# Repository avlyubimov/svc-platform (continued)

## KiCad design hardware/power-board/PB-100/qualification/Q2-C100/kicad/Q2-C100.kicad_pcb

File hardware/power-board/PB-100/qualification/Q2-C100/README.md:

# Q2-C100 Qualification Coupon

Status: `PAUSED DIAGNOSTIC COUPON / FABRICATION BLOCKED`

Q2-C100 is the optional diagnostic laboratory coupon described by
`PB-100-q2-empirical-qualification-plan.md`. It is not PB-100, is not a vehicle
assembly and does not itself authorize `PB-100.kicad_pcb`; ADR-0020 separately
authorizes the full PB-100 Rev.1 EVT layout and its own controlled fab review.
Further coupon development is paused and coupon fabrication is not a prerequisite
for PB-100 EVT layout, fabrication or validation.

The committed KiCad milestone contains:

- the exact `IAUTN15S6N025ATMA1` QDUT and `LM74930QRGERQ1` UCTRL footprints;
- the selected `IAUT300N08S5N012ATMA2` QREV correlation path;
- separate RAW drain, common-source and system-output REDCUBE terminals;
- a direct UCTRL HGATE-to-QDUT gate connection with no Rg or CdV/dt element;
- Kelvin and fixture probe interfaces, isolated heater and TSEP interfaces;
- the routed high-current path, direct HGATE path, DGATE path, controller
  A/OUT Kelvin returns and every remaining pad-to-pad control/fixture
  connection;
- a four-layer, 2.0 mm preliminary stackup boundary and a 2.0 mm RAW_101V
  clearance rule outside the unavoidable reviewed QDUT/RVS/ROV component
  geometries;
- seven independent source spokes per TOLL, 4.0 mm source collection buses,
  reinforced outer-layer power corridors and two five-via transition rows at
  each common-source package boundary;
- exact AEC-Q200 Vishay CRCW-HP RVS/ROV resistors and exact TDK soft-termination
  CCAP, each with an independent controlled alternative.
- exact 2/3/4-position Molex Micro-Fit `436500228`, `436500328` and
  `436500428` board headers and mating harness kits, with the 2.0 mm versus
  recommended 1.57 mm fit mismatch kept open;
- exact Harwin `S1751-46R` SMT probe-attachment hardware, without treating it
  as voltage-, bandwidth- or touch-safety evidence.

KiCad 10.0.4 ERC has zero findings. Board DRC has zero rule violations and
zero unconnected items. CI also pins the four-layer routing set, direct F.Cu HGATE
path, separate internal Kelvin/sense layers, outer-layer power-spine widths,
power-via stitching, 0.20 mm default clearance and 2.0 mm RAW_101V clearance
rule. `Q2-C100-pre-fab-screening.md` reproducibly calculates the known copper
cross-sections, a 3.0453 W straight-corridor hot-loss lower bound and the
194.75 nH absolute waveform-derived loop ceiling. None is a thermal or
extracted-inductance pass. This electrical-routing milestone is not permission
to fabricate.

## Build variants

`CORRELATION-A` populates UCTRL and QREV. UCTRL drives QDUT directly and the
input rise/OV-deglitch behavior is measured.

`FORCED-B` does not populate UCTRL or QREV. The isolated external driver is
connected to JDRIVE pins 1 (gate) and 2 (source Kelvin). Its complete discharge
waveform must be demonstrated to be no stronger than the LM74930-Q1 worst-case
corner before Phase B. The copper between the QDUT gate, JDRIVE and probe points
does not contain a selector, zero-ohm resistor or hidden damping part.

Population differences are controlled by `Q2-C100-assembly-variants.csv`.

## Hard safety boundary

Do not energize or fabricate this revision. Before the status can change to
`FAB-REVIEW`, the supplier stackup/creepage, thermal/current-density and loop-
inductance reviews, 2.0 mm Micro-Fit fit/DFM, exact instrument/probe and
external safety-interface MPNs, interlock behavior, external current limiting,
stored-energy discharge, enclosure/shield, remote trigger, instrument ratings,
heater control and laboratory safety review must close. Board interface
selection is recorded in `Q2-C100-fixture-interface-selection.md` and does not
make exposed connectors or test points touch-safe.
Gerber, drill, pick-and-place and manufacturing ZIP files are prohibited in the
current state.

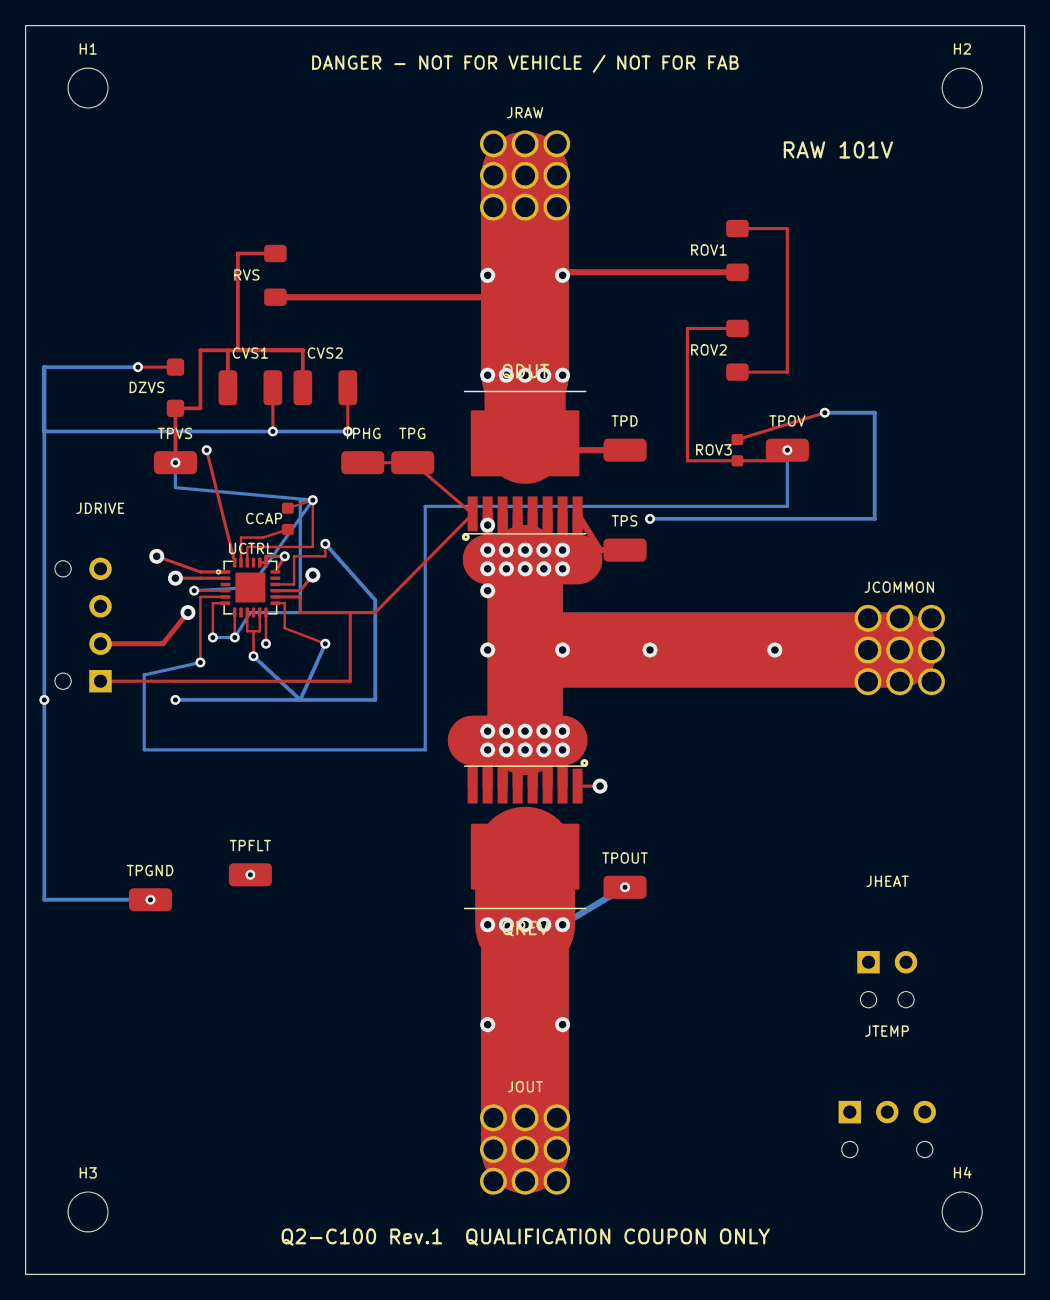
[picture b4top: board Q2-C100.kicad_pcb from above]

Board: 4 copper layers, 80.0 x 100.0 mm, 30 parts (0 on the bottom side), 11 nets.

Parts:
CCAP: CGA3E2X7R1H104K080AE 100nF 50V X7R; R_C_0603_1608Metric
CVS1, CVS2: CGA6N3X7R2A225M230AE 2.2uF 100V X7R; C_1210_3225Metric
DZVS: BZT52H-B56-Q 56V; SOD123F
H1, H2, H3, H4: M3 NPTH; MountingHole_M3_NPTH
JCOMMON: 786202073 REDCUBE M3 130A COMMON; REDCUBE_786202073_3x3_P2.54
JDRIVE: 436500428 MICRO-FIT 4POS DRIVER; MicroFit_43650_0428_Vertical_R90
JHEAT: 436500228 MICRO-FIT 2POS HEATER; MicroFit_43650_0228_Vertical
JOUT: 786202073 REDCUBE M3 130A OUT; REDCUBE_786202073_3x3_P2.54
JRAW: 786202073 REDCUBE M3 130A RAW; REDCUBE_786202073_3x3_P2.54
JTEMP: 436500328 MICRO-FIT 3POS TEMP; MicroFit_43650_0328_Vertical
QDUT: IAUTN15S6N025ATMA1; PG-HSOF-8-1_TOLL_Infineon
QREV: IAUT300N08S5N012ATMA2; PG-HSOF-8-1_TOLL_Infineon
ROV1, ROV2: CRCW120642K2FKEAHP 42.2k 1%; R_1206_3216Metric
ROV3: CRCW06031K00FKEAHP 1.00k 1%; R_C_0603_1608Metric
RVS: CRCW120610K0FKEAHP 10.0k 1%; R_1206_3216Metric
TPD: S1751-46R QDUT_DRAIN_KELVIN; Harwin_S1751-46R
TPFLT: S1751-46R FAULT_PROBE; Harwin_S1751-46R
TPG: S1751-46R QDUT_GATE_KELVIN; Harwin_S1751-46R
TPGND: S1751-46R PROBE_GND; Harwin_S1751-46R
TPHG: S1751-46R UCTRL_HGATE_PROBE; Harwin_S1751-46R
TPOUT: S1751-46R SYSTEM_OUT_PROBE; Harwin_S1751-46R
TPOV: S1751-46R OV_TRIGGER_PROBE; Harwin_S1751-46R
TPS: S1751-46R QDUT_SOURCE_KELVIN; Harwin_S1751-46R
TPVS: S1751-46R CTRL_VS_PROBE; Harwin_S1751-46R
UCTRL: LM74930QRGERQ1; VQFN-24_RGE_4x4mm_P0.5mm_EP2.4mm

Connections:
COMMON_SOURCE: JCOMMON.1 (POWER), JDRIVE.2 (SOURCE_K), QDUT.2 (S), QDUT.3 (S), QDUT.4 (S), QDUT.5 (S), QDUT.6 (S), QDUT.7 (S), QDUT.8 (S), QREV.2 (S), QREV.3 (S), QREV.4 (S), QREV.5 (S), QREV.6 (S), QREV.7 (S), QREV.8 (S), TPS.1 (TP), UCTRL.2 (A), UCTRL.15 (OUT)
CTRL_CAP: CCAP.1, UCTRL.23 (CAP)
CTRL_FLT_N: TPFLT.1 (TP), UCTRL.12 (FLT)
CTRL_OV: ROV2.2, ROV3.1, TPOV.1 (TP), UCTRL.5 (OV)
CTRL_VS: CCAP.2, CVS1.1, CVS2.1, DZVS.1 (K), RVS.2, TPVS.1 (TP), UCTRL.4 (UVLO), UCTRL.6 (EN), UCTRL.7 (MODE), UCTRL.22 (VS)
GND: CVS1.2, CVS2.2, DZVS.2 (A), ROV3.2, TPGND.1 (TP), UCTRL.9 (TMR), UCTRL.11 (ILIM), UCTRL.13 (GND), UCTRL.16 (OVCLAMP)
OV_MID: ROV1.2, ROV2.1
Q2_HGATE: JDRIVE.1 (GATE), QDUT.1 (G), TPG.1 (TP), TPHG.1 (TP), UCTRL.14 (HGATE)
QREV_DGATE: QREV.1 (G), UCTRL.1 (DGATE)
RAW_101V: JRAW.1 (POWER), QDUT.Tab (D), ROV1.1, RVS.1, TPD.1 (TP)
SYSTEM_OUT: JOUT.1 (POWER), QREV.Tab (D), TPOUT.1 (TP), UCTRL.18 (ISCP), UCTRL.19 (CS-), UCTRL.20 (CS+), UCTRL.24 (C)

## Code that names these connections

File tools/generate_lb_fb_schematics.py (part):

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

STM32_NAMES = [
    "PE2", "PE3", "PE4", "PE5", "PE6", "VBAT", "PC13", "PC14-OSC32_IN", "PC15-OSC32_OUT", "VSS",
    "VDD", "PH0-OSC_IN", "PH1-OSC_OUT", "NRST", "PC0", "PC1", "PC2", "PC3", "VSSA", "VREF-",
    "VREF+", "VDDA", "PA0", "PA1", "PA2", "PA3", "VSS", "VDD", "PA4", "PA5", "PA6", "PA7",
    "PC4", "PC5", "PB0", "PB1", "PB2", "PE7", "PE8", "PE9", "PE10", "PE11", "PE12", "PE13",
    "PE14", "PE15", "PB10", "VCAP1", "VSS", "VDD", "PB12", "PB13", "PB14", "PB15", "PD8", "PD9",
    "PD10", "PD11", "PD12", "PD13", "PD14", "PD15", "PC6", "PC7", "PC8", "PC9", "PA8", "PA9",
    "PA10", "PA11-USB_DM", "PA12-USB_DP", "PA13-SWDIO", "VDDUSB", "VSS", "VDD", "PA14-SWCLK",
    "PA15", "PC10", "PC11", "PC12", "PD0", "PD1", "PD2", "PD3", "PD4", "PD5", "PD6", "PD7",
    "PB3-SWO", "PB4", "PB5", "PB6", "PB7", "BOOT0", "PB8", "PB9", "PE0", "VCAP2", "VSS", "VDD",
]


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        "sustained and 381.2 mA service-peak budgets including FB-100 worst-case indication; ADR-0015 "
        "CAN1 FDCAN/read-only ownership with no LB "
        "transceiver; CAN1_TX_ROUTE remains the PB DNP/open route. TCA9539-Q1 maps the ten role-free channel LEDs "
        "and slow UI signals and powers up with all ports as inputs. STM32 PD7 directly drives the timing-critical "
        "LTC3212 LEDEN path. CAN2/LIN/RS485 footprints are DNP by default. USB VBUS uses a 5 V-tolerant "
        "SN74LVC1G17-Q1 digital detector with a defined raw-input pulldown and cannot back-power PB_5V_OUT, "
        "LB_3V3_MAIN, or LB_3V3_IO. Three RADIO_SENSOR_3V3-powered SN74LVC1G125-Q1 buffers isolate both "
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        "keep every E73 digital pin within its unpowered limit. Dedicated top-side test pads expose the module's "
        "own SWDIO, SWDCLK, reset, switched 3.3 V reference, and GND for first programming and recovery. "
        "ADC_REF is sourced and locally decoupled; AGND returns to GND at one documented zero-ohm point. Reviewed footprint "
        "FOG_A_SW_IN and FOG_B_SW_IN are independent protected requests on PA8 and PA9. PB-100 owns the "
        "primary cable-entry suppressor; each LB path has a dry-contact series path, a pull-up, RC filtering, a 4.3 V clamp and an "
        "automotive Schmitt buffer; mutually exclusive DNP transistor paths support a measured 12 V switch variant. "
        "Neither input directly drives an output. Reviewed footprint binding and mechanical envelope remain governed by LB-100-pcb-layout-start-checklist.csv, "
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
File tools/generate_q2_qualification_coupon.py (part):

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                "Correlation build: populate UCTRL and QREV; HGATE is direct to QDUT gate.",
                "Forced build: do not populate UCTRL/QREV; drive QDUT at JDRIVE pins 1/2.",
                "No populated Rg or CdV/dt exists in either accepted build.",
                "RAW_101V may reach 101 V; LM74930 protected pins remain on <=65 V nets.",
                "All pad-to-pad electrical connections are routed; FAB-REVIEW remains open.",
            )
        ),
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    )

    terminal_fp = "Q2C100:REDCUBE_786202073_3x3_P2.54"
    terminal_pin = [("1", "POWER", "RAW_101V")]
    schematic.add(c("JRAW", "786202073 REDCUBE M3 130A RAW", terminal_fp, WURTH_TERMINAL_DS, terminal_pin))
    schematic.add(c("JCOMMON", "786202073 REDCUBE M3 130A COMMON", terminal_fp, WURTH_TERMINAL_DS, [("1", "POWER", "COMMON_SOURCE")]))
    schematic.add(c("JOUT", "786202073 REDCUBE M3 130A OUT", terminal_fp, WURTH_TERMINAL_DS, [("1", "POWER", "SYSTEM_OUT")]))
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    )

    controller_pins = (
        Pin("1", "DGATE", "QREV_DGATE", "output"),
        Pin("2", "A", "COMMON_SOURCE", "input"),
        Pin("3", "SW", None, "no_connect"),
        Pin("4", "UVLO", "CTRL_VS", "input"),
        Pin("5", "OV", "CTRL_OV", "input"),
        Pin("6", "EN", "CTRL_VS", "input"),
        Pin("7", "MODE", "CTRL_VS", "input"),
        Pin("8", "N.C.", None, "no_connect"),
        Pin("9", "TMR", "GND", "input"),
        Pin("10", "IMON", None, "no_connect"),
        Pin("11", "ILIM", "GND", "input"),
        Pin("12", "FLT", "CTRL_FLT_N", "open_collector"),
        Pin("13", "GND", "GND", "power_in"),
        Pin("14", "HGATE", "Q2_HGATE", "output"),
        Pin("15", "OUT", "COMMON_SOURCE", "input"),
        Pin("16", "OVCLAMP", "GND", "input"),
        Pin("17", "N.C.", None, "no_connect"),
        Pin("18", "ISCP", "SYSTEM_OUT", "input"),
        Pin("19", "CS-", "SYSTEM_OUT", "input"),
        Pin("20", "CS+", "SYSTEM_OUT", "input"),
        Pin("21", "N.C.", None, "no_connect"),
        Pin("22", "VS", "CTRL_VS", "power_in"),
        Pin("23", "CAP", "CTRL_CAP", "output"),
        Pin("24", "C", "SYSTEM_OUT", "input"),
        Pin("25", "RTN", None, "no_connect"),
    )
    schematic.add(
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        routes.extend(
            [
                segment(net_codes, "RAW_101V", layer, 7.0, (40.0, 12.0), (40.0, 28.0), "raw-main"),
                segment(net_codes, "COMMON_SOURCE", layer, 6.0, (40.0, 43.0), (40.0, 57.0), "common-spine"),
                segment(net_codes, "COMMON_SOURCE", layer, 6.0, (40.0, 50.0), (70.0, 50.0), "common-terminal"),
                segment(net_codes, "SYSTEM_OUT", layer, 7.0, (40.0, 72.0), (40.0, 90.0), "out-main"),
            ]
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    routes.extend(route_path(net_codes, "CTRL_VS", "F.Cu", 0.3, ((12.0, 35.0), (12.0, 30.65)), "vs-probe"))
    routes.append(signal_via(net_codes, "CTRL_VS", 23.0, 38.0, "vs-controller"))
    routes.extend(route_path(net_codes, "CTRL_VS", "B.Cu", 0.25, ((12.0, 35.0), (12.0, 37.0), (23.0, 38.0)), "vs-controller"))
    routes.extend(route_path(net_codes, "CTRL_VS", "F.Cu", 0.20, ((17.75, 43.0), (17.75, 41.75), (20.0, 41.75), (23.0, 41.75), (23.0, 38.0), (21.0, 38.65)), "vs-pin22-ccap"))
    routes.append(signal_via(net_codes, "CTRL_VS", 13.5, 45.25, "vs-pin4"))
    routes.extend(route_path(net_codes, "CTRL_VS", "F.Cu", 0.20, ((16.0, 45.25), (13.5, 45.25)), "vs-pin4"))
    routes.extend(route_path(net_codes, "CTRL_VS", "B.Cu", 0.25, ((13.5, 45.25), (18.0, 45.0), (23.0, 38.0)), "vs-pin4"))
    routes.append(signal_via(net_codes, "CTRL_VS", 15.0, 49.0, "vs-pin6"))
    routes.append(signal_via(net_codes, "CTRL_VS", 16.75, 49.0, "vs-pin7"))
    routes.extend(route_path(net_codes, "CTRL_VS", "F.Cu", 0.20, ((16.0, 46.25), (15.0, 46.25), (15.0, 49.0)), "vs-pin6"))
    routes.extend(route_path(net_codes, "CTRL_VS", "F.Cu", 0.20, ((16.75, 47.0), (16.75, 49.0)), "vs-pin7"))
    routes.extend(route_path(net_codes, "CTRL_VS", "B.Cu", 0.25, ((15.0, 49.0), (16.75, 49.0), (18.0, 47.0), (22.0, 47.0), (22.0, 38.0), (23.0, 38.0)), "vs-pin6-7"))

    routes.extend(route_path(net_codes, "CTRL_CAP", "F.Cu", 0.20, ((17.25, 43.0), (17.25, 41.0), (19.0, 41.0), (21.0, 40.35)), "cap-local"))

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    routes.extend(route_path(net_codes, "GND", "B.Cu", 0.3, ((18.25, 50.5), (22.0, 54.0)), "gnd-controller-b"))
    routes.extend(route_path(net_codes, "GND", "B.Cu", 0.3, ((24.0, 49.5), (22.0, 54.0)), "gnd-controller-c"))

    # All four protected-side controller sense pins join SYSTEM_OUT on In1.Cu,
    # clear of the existing DGATE route.  TPOUT then joins the B.Cu power path.
    for token, start, fanout in (
        ("out-group", (20.0, 43.75), (20.75, 42.5)),
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    ):
        routes.append(signal_via(net_codes, "SYSTEM_OUT", fanout[0], fanout[1], token))
        routes.extend(route_path(net_codes, "SYSTEM_OUT", "F.Cu", 0.25, (start, fanout), token))
    routes.extend(route_path(net_codes, "SYSTEM_OUT", "F.Cu", 0.25, ((18.75, 43.0), (19.25, 43.0), (19.25, 42.5), (20.75, 42.5)), "out-pins18-20"))
    routes.extend(route_path(net_codes, "SYSTEM_OUT", "In1.Cu", 0.25, ((14.5, 34.0), (20.75, 42.5), (26.0, 43.75), (30.0, 44.0), (30.0, 59.5), (48.0, 59.5), (48.0, 69.0)), "out-sense"))
    routes.extend(route_path(net_codes, "SYSTEM_OUT", "B.Cu", 0.5, ((48.0, 69.0), (43.0, 72.0)), "out-probe"))

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
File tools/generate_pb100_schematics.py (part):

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            "GND",
        )
    )
    schematic.add(resistor("RSN1", "100R DNP Q1 DAMPING", "VBAT_REV_PROT", "Q1_SNUB", dnp=True))
    schematic.add(capacitor("CSN1", "1nF 100V C0G DNP", "Q1_SNUB", "INPUT_COMMON_SOURCE", dnp=True))
    schematic.add(resistor("RSN2", "100R DNP Q2 DAMPING", "VBAT_RAW", "Q2_SNUB", dnp=True))
    schematic.add(capacitor("CSN2", "1nF 200V C0G DNP", "Q2_SNUB", "INPUT_COMMON_SOURCE", dnp=True))

    schematic.add(
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
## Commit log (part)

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2026-06-30 Initial SVC platform structure
2026-06-30 docs: freeze architecture baseline
2026-06-30 docs: select initial component families
2026-06-30 docs: define pb100 current budget
2026-06-30 docs: start implementation after architecture freeze
2026-06-30 hardware: add pb100 schematic input tables
2026-06-30 hardware: select pb100 power path candidates
2026-06-30 hardware: add pb100 preliminary validation
2026-06-30 hardware: add pb100 schematic freeze checklist
2026-06-30 hardware: use external controllers for low-current outputs
2026-06-30 hardware: add pb100 b2b pin map
2026-06-30 hardware: define can1 tx disable input
2026-06-30 hardware: define pb100 input reverse fet strategy
2026-06-30 hardware: define pb100 out2 soa envelope
2026-06-30 test: add pb100 bench validation matrix
2026-06-30 hardware: define pb100 logic power rails
2026-06-30 hardware: define pb100 current telemetry
2026-06-30 hardware: define pb100 thermal telemetry
2026-06-30 hardware: mark pb100 schematic planning ready for review
2026-06-30 hardware: add pb100 kicad preparation plan
2026-06-30 hardware: add pb100 schematic capture contract
2026-06-30 hardware: add pb100 kicad schematic scaffold
2026-06-30 hardware: add pb100 kicad child sheet placeholders
2026-06-30 hardware: add pb100 preliminary kicad symbols
2026-06-30 tools: add pb100 artifact validator
2026-06-30 hardware: define pb100 garage connector plan
2026-06-30 firmware: add power budget service
2026-06-30 firmware: add output manager core
2026-06-30 firmware: add battery protection service
2026-06-30 firmware: add event bus core
2026-06-30 firmware: add can safety guard
2026-06-30 ci: run pb100 and firmware checks
2026-06-30 docs: update project status and validation
2026-06-30 build: add root project checks
2026-06-30 firmware: add system safety coordinator
2026-06-30 firmware: add event dispatcher
2026-06-30 build: rebuild firmware tests on header changes
2026-06-30 firmware: add configuration validator
2026-06-30 tools: validate firmware config json
2026-06-30 firmware: add config json schema
2026-06-30 firmware: add role-based rule actions
2026-06-30 firmware: add rule condition state
2026-06-30 firmware: add in-memory rule runner
2026-06-30 firmware: add initial rule text parser
2026-06-30 firmware: add output pwm state
2026-06-30 firmware: compile rule text to runner
2026-06-30 tools: block pb100 layout artifacts
2026-06-30 docs: refresh project implementation status
2026-06-30 firmware: add telemetry snapshot service
2026-06-30 firmware: use telemetry snapshots in safety paths
2026-06-30 firmware: add event log ring buffer
2026-06-30 tools: run optional pb100 kicad erc
2026-06-30 firmware: add thermal protection service
2026-06-30 firmware: apply thermal cutoff through system safety
2026-06-30 docs: add final readiness gates
2026-06-30 tools: validate pb100 kicad netlist export
2026-06-30 tools: block pb100 kicad role tokens
2026-06-30 hardware: add pb100 symbol mpn readiness gate
2026-06-30 hardware: add pb100 symbol capture worklist
2026-06-30 hardware: add initial pb100 concrete symbols
2026-06-30 hardware: validate pb100 symbol pin evidence
2026-06-30 hardware: add pb100 passive class symbols
2026-06-30 hardware: add pb100 mosfet preliminary symbols
2026-06-30 hardware: add pb100 jpb1 preliminary symbol
2026-06-30 tools: guard pending pb100 symbols
2026-06-30 hardware: add pb100 output fuse symbol
2026-06-30 hardware: map pb100 instances to symbols
2026-06-30 hardware: map pb100 instances to sheets
2026-06-30 hardware: add pb100 kicad sheet manifest
2026-06-30 hardware: add pb100 schematic net domain plan
2026-06-30 production: map pb100 symbols to bom
2026-06-30 hardware: add pb100 schematic readiness contracts
2026-06-30 hardware: add pb100 output controller template
2026-06-30 hardware: add pb100 input power pin templates
2026-06-30 hardware: track pb100 schematic freeze gaps
2026-06-30 hardware: add pb100 design value placeholders
2026-06-30 hardware: add pb100 can1 safety verification
2026-06-30 production: add pb100 sourcing recheck register
2026-06-30 hardware: trace pb100 freeze validation
2026-06-30 hardware: expand pb100 output nets
2026-06-30 hardware: plan pb100 test points
2026-06-30 hardware: define pb100 fault responses
2026-06-30 hardware: queue pb100 schematic capture
2026-06-30 hardware: mark pb100 kicad capture work
2026-06-30 firmware: add pb100 hardware capabilities
